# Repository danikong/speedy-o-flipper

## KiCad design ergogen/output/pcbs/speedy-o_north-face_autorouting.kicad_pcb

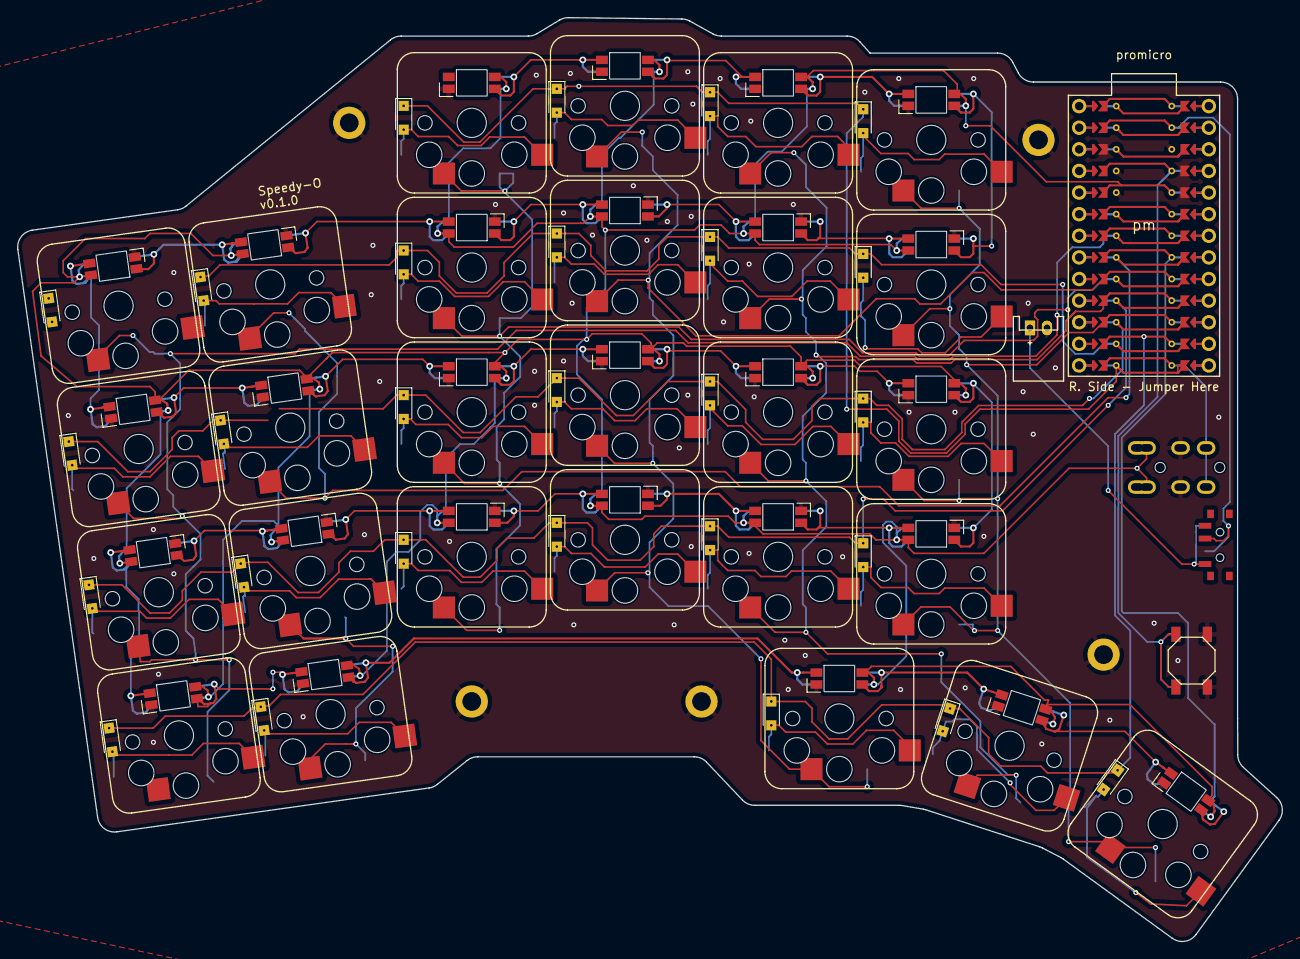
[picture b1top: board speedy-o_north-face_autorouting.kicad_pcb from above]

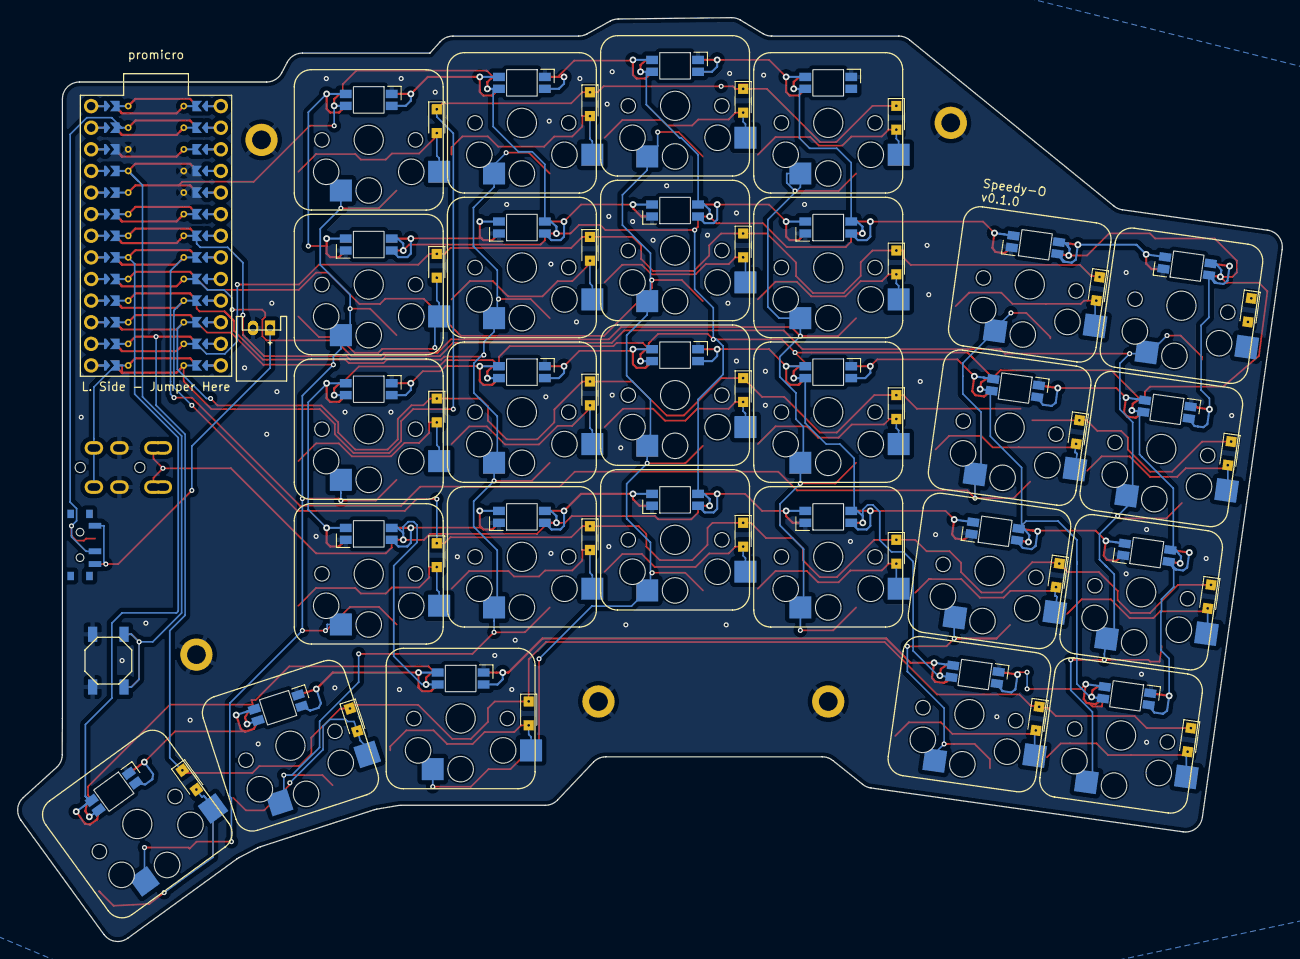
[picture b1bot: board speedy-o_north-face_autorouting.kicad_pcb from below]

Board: 2 copper layers, 148.6 x 108.6 mm, 93 parts (27 on the bottom side), 71 nets.

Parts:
B1, B2: SW_TACT_ALPS_SKQGABE010
D1, D2, D3, D4, D5, D6, D7, D8, D9, D10, D11, D12, D13, D14, D15, D16, D17, D18, D19, D20, D21, D22, D23, D24, D25, D26, D27: Nexperia_CFP3_SOD-123W
H1, H2, H3, H4, H5: mounting_hole_plated
JST1, JST2: JST_PH_S2B-PH-K_02x2.00mm_Angled
LED1, LED2, LED3, LED4, LED5, LED6, LED7, LED8, LED9, LED10, LED11, LED12, LED13, LED14, LED15, LED16, LED17, LED18, LED19, LED20, LED21, LED22, LED23, LED24, LED25, LED26, LED27: led_SK6812mini-e (per-key, reversible)
S1, S2, S3, S4, S5, S6, S7, S8, S9, S10, S11, S12, S13, S14, S15, S16, S17, S18, S19, S20, S21, S22, S23, S24, S25, S26, S27: PG1350
T1: SW_SPDT_PCM12
TRRS: TRRS-PJ-320A-dual
pm: ProMicro

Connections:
GND: B1.1, B2.1, JST1.2, JST2.2, LED1.3, LED2.3, LED3.3, LED4.3, LED5.3, LED6.3, LED7.3, LED8.3, LED9.3, LED10.3, LED11.3, LED12.3, LED13.3, LED14.3, LED15.3, LED16.3, LED17.3, LED18.3, LED19.3, LED20.3, LED21.3, LED22.3, LED23.3, LED24.3, LED25.3, LED26.3, LED27.3, TRRS.3, pm.3, pm.4, pm.23
P3: S1.1, S2.1, S3.1, S4.1, pm.6
P4: S5.1, S6.1, S7.1, S8.1, pm.7
P5: S9.1, S10.1, S11.1, S12.1, pm.8
P6: D1.1, D5.1, D10.1, D14.1, D17.1, D21.1, pm.9
P7: D2.1, D6.1, D11.1, D15.1, D18.1, D22.1, pm.10
P8: D3.1, D7.1, D12.1, D16.1, D19.1, D23.1, pm.11
P9: D4.1, D8.1, D20.1, D24.1, pm.12
P10: TRRS.4, pm.13
P14: S21.1, S22.1, S23.1, S24.1, S27.1, pm.15
P15: S17.1, S18.1, S19.1, S20.1, S26.1, pm.16
P16: D9.1, D13.1, D25.1, D26.1, D27.1, pm.14
P18: S13.1, S14.1, S15.1, S16.1, S25.1, pm.17
P19: LED27.2, pm.18
RAW: T1.2, pm.24
RST: B1.2, B2.2, pm.22
VCC: LED1.1, LED2.1, LED3.1, LED4.1, LED5.1, LED6.1, LED7.1, LED8.1, LED9.1, LED10.1, LED11.1, LED12.1, LED13.1, LED14.1, LED15.1, LED16.1, LED17.1, LED18.1, LED19.1, LED20.1, LED21.1, LED22.1, LED23.1, LED24.1, LED25.1, LED26.1, LED27.1, TRRS.2, pm.21
main_index_bottom: D1.2, S17.2
main_index_home: D2.2, S18.2
main_index_num: D4.2, S20.2
main_index_top: D3.2, S19.2
main_inner_bottom: D5.2, S21.2
main_inner_home: D6.2, S22.2
main_inner_num: D8.2, S24.2
main_inner_top: D7.2, S23.2
main_middle_bottom: D21.2, S13.2
main_middle_home: D22.2, S14.2
main_middle_num: D24.2, S16.2
main_middle_top: D23.2, S15.2
main_outer_bottom: D9.2, S1.2
main_outer_home: D10.2, S2.2
main_outer_num: D12.2, S4.2
main_outer_top: D11.2, S3.2
main_pinky_bottom: D13.2, S5.2
main_pinky_home: D14.2, S6.2
main_pinky_num: D16.2, S8.2
main_pinky_top: D15.2, S7.2
main_ring_bottom: D17.2, S9.2
main_ring_home: D18.2, S10.2
main_ring_num: D20.2, S12.2
main_ring_top: D19.2, S11.2
pos: JST1.1, JST2.1, T1.1
rgb_main_index_bottom: LED13.4, LED17.2
rgb_main_index_home: LED18.2, LED22.4
rgb_main_index_num: LED20.2, LED24.4
rgb_main_index_top: LED15.4, LED19.2
rgb_main_inner_bottom: LED17.4, LED21.2
rgb_main_inner_home: LED21.4, LED22.2
rgb_main_inner_num: LED23.4, LED24.2
rgb_main_inner_top: LED19.4, LED23.2
rgb_main_middle_bottom: LED9.4, LED13.2
rgb_main_middle_home: LED14.2, LED18.4
rgb_main_middle_num: LED16.2, LED20.4
rgb_main_middle_top: LED11.4, LED15.2
rgb_main_outer_bottom: LED1.2, LED5.4
rgb_main_outer_home: LED1.4, LED2.2
rgb_main_outer_num: LED3.4, LED4.2
rgb_main_outer_top: LED3.2, LED7.4
rgb_main_pinky_bottom: LED5.2, LED25.4
rgb_main_pinky_home: LED2.4, LED6.2
rgb_main_pinky_num: LED4.4, LED8.2
rgb_main_pinky_top: LED7.2, LED10.4
rgb_main_ring_bottom: LED6.4, LED9.2
rgb_main_ring_home: LED10.2, LED14.4
rgb_main_ring_num: LED12.2, LED16.4
rgb_main_ring_top: LED8.4, LED11.2
rgb_thumb_home_home: LED26.2, LED27.4
rgb_thumb_outer_home: LED25.2, LED26.4
thumb_home_home: D26.2, S26.2
thumb_inner_home: D27.2, S27.2
thumb_outer_home: D25.2, S25.2

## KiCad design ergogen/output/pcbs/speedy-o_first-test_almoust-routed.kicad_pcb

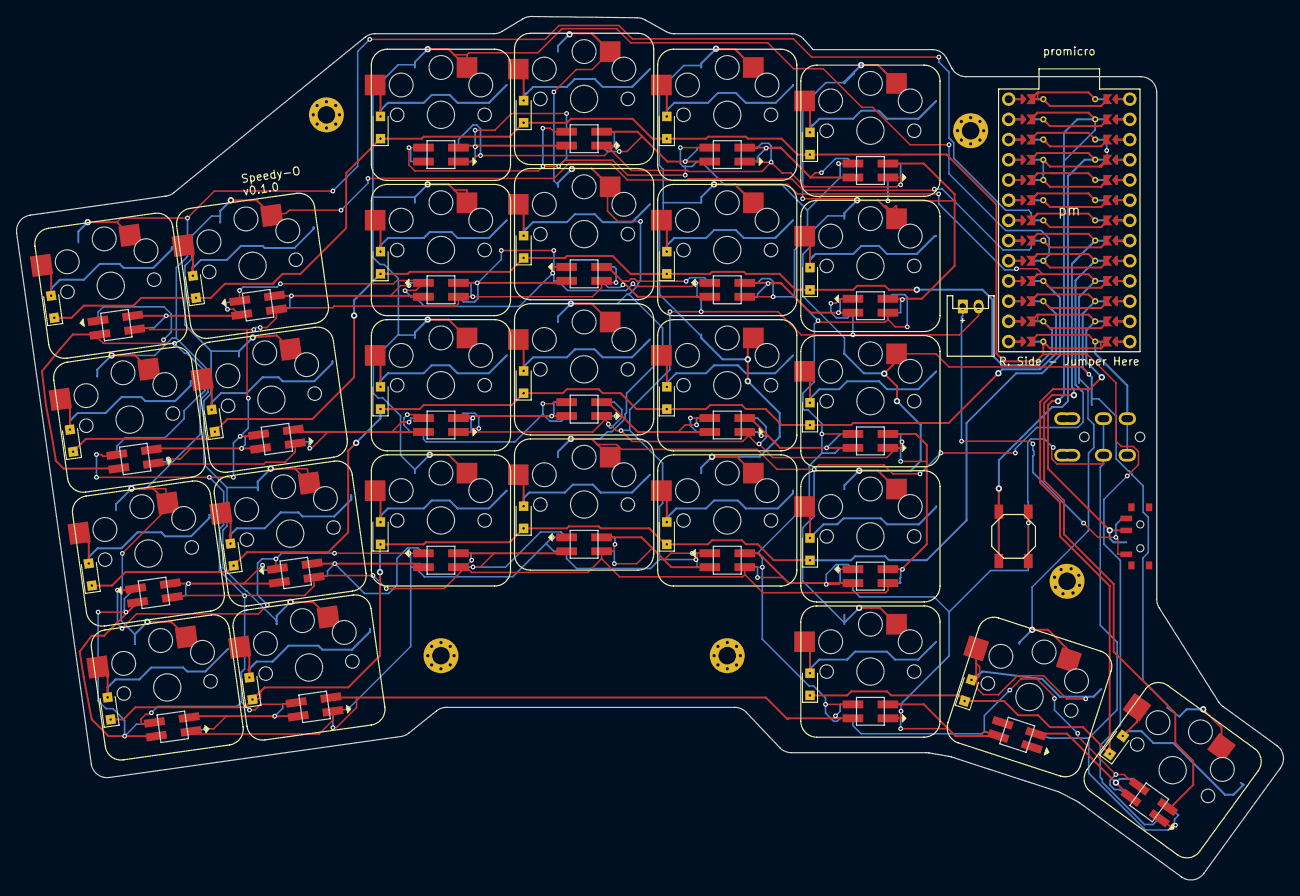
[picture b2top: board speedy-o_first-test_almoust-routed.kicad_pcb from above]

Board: 2 copper layers, 159.3 x 108.6 mm, 93 parts (0 on the bottom side), 71 nets.

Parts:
B1, B2: SW_TACT_ALPS_SKQGABE010
D1, D2, D3, D4, D5, D6, D7, D8, D9, D10, D11, D12, D13, D14, D15, D16, D17, D18, D19, D20, D21, D22, D23, D24, D25, D26, D27: Nexperia_CFP3_SOD-123W
JST1, JST2: JST_PH_S2B-PH-K_02x2.00mm_Angled
LED1, LED2, LED3, LED4, LED5, LED6, LED7, LED8, LED9, LED10, LED11, LED12, LED13, LED14, LED15, LED16, LED17, LED18, LED19, LED20, LED21, LED22, LED23, LED24, LED25, LED26, LED27: WS2812B
S1, S2, S3, S4, S5, S6, S7, S8, S9, S10, S11, S12, S13, S14, S15, S16, S17, S18, S19, S20, S21, S22, S23, S24, S25, S26, S27: PG1350
T1: SW_SPDT_PCM12
TRRS1: TRRS-PJ-320A-dual
_2, _3, _4, _5, _6: MountingHole_2.2mm_M2_Pad_Via
pm: ProMicro

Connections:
GND: B1.1, B2.1, JST1.2, JST2.2, LED1.3, LED2.3, LED3.3, LED4.3, LED5.3, LED6.3, LED7.3, LED8.3, LED9.3, LED10.3, LED11.3, LED12.3, LED13.3, LED14.3, LED15.3, LED16.3, LED17.3, LED18.3, LED19.3, LED20.3, LED21.3, LED22.3, LED23.3, LED24.3, LED25.3, LED26.3, LED27.3, TRRS1.3, pm.3, pm.4, pm.23
P3: S1.1, S2.1, S3.1, S4.1, pm.6
P4: S5.1, S6.1, S7.1, S8.1, pm.7
P5: S9.1, S10.1, S11.1, S12.1, pm.8
P6: D1.1, D5.1, D9.1, D13.1, D17.1, D21.1, pm.9
P7: D2.1, D6.1, D10.1, D14.1, D18.1, D22.1, pm.10
P8: D3.1, D7.1, D11.1, D15.1, D19.1, D23.1, pm.11
P9: D4.1, D8.1, D12.1, D16.1, D20.1, D24.1, LED27.4, pm.12
P10: TRRS1.4, pm.13
P14: S21.1, S22.1, S23.1, S24.1, S27.1, pm.15
P15: S17.1, S18.1, S19.1, S20.1, S26.1, pm.16
P16: D25.1, D26.1, D27.1, pm.14
P18: S13.1, S14.1, S15.1, S16.1, S25.1, pm.17
P19: LED27.4, pm.18
RAW: T1.2, pm.24
RST: B1.2, B2.2, pm.22
VCC: LED1.1, LED2.1, LED3.1, LED4.1, LED5.1, LED6.1, LED7.1, LED8.1, LED9.1, LED10.1, LED11.1, LED12.1, LED13.1, LED14.1, LED15.1, LED16.1, LED17.1, LED18.1, LED19.1, LED20.1, LED21.1, LED22.1, LED23.1, LED24.1, LED25.1, LED26.1, LED27.1, TRRS1.2, pm.21
main_index_bottom: D17.2, S17.2
main_index_home: D18.2, S18.2
main_index_num: D20.2, S20.2
main_index_top: D19.2, S19.2
main_inner_bottom: D21.2, S21.2
main_inner_home: D22.2, S22.2
main_inner_num: D24.2, S24.2
main_inner_top: D23.2, S23.2
main_middle_bottom: D13.2, S13.2
main_middle_home: D14.2, S14.2
main_middle_num: D16.2, S16.2
main_middle_top: D15.2, S15.2
main_outer_bottom: D1.2, S1.2
main_outer_home: D2.2, S2.2
main_outer_num: D4.2, S4.2
main_outer_top: D3.2, S3.2
main_pinky_bottom: D5.2, S5.2
main_pinky_home: D6.2, S6.2
main_pinky_num: D8.2, S8.2
main_pinky_top: D7.2, S7.2
main_ring_bottom: D9.2, S9.2
main_ring_home: D10.2, S10.2
main_ring_num: D12.2, S12.2
main_ring_top: D11.2, S11.2
pos: JST1.1, JST2.1, T1.1
rgb_main_index_bottom: LED13.2, LED17.4
rgb_main_index_home: LED18.4, LED22.2
rgb_main_index_num: LED20.4, LED24.2
rgb_main_index_top: LED15.2, LED19.4
rgb_main_inner_bottom: LED17.2, LED21.4
rgb_main_inner_home: LED21.2, LED22.4
rgb_main_inner_num: LED23.2, LED24.4
rgb_main_inner_top: LED19.2, LED23.4
rgb_main_middle_bottom: LED9.2, LED13.4
rgb_main_middle_home: LED14.4, LED18.2
rgb_main_middle_num: LED16.4, LED20.2
rgb_main_middle_top: LED11.2, LED15.4
rgb_main_outer_bottom: LED1.4, LED5.2
rgb_main_outer_home: LED1.2, LED2.4
rgb_main_outer_num: LED3.2, LED4.4
rgb_main_outer_top: LED3.4, LED7.2
rgb_main_pinky_bottom: LED5.4, LED25.2
rgb_main_pinky_home: LED2.2, LED6.4
rgb_main_pinky_num: LED4.2, LED8.4
rgb_main_pinky_top: LED7.4, LED10.2
rgb_main_ring_bottom: LED6.2, LED9.4
rgb_main_ring_home: LED10.4, LED14.2
rgb_main_ring_num: LED12.4, LED16.2
rgb_main_ring_top: LED8.2, LED11.4
rgb_thumb_home_home: LED26.4, LED27.2
rgb_thumb_outer_home: LED25.4, LED26.2
thumb_home_home: D26.2, S26.2
thumb_inner_home: D27.2, S27.2
thumb_outer_home: D25.2, S25.2

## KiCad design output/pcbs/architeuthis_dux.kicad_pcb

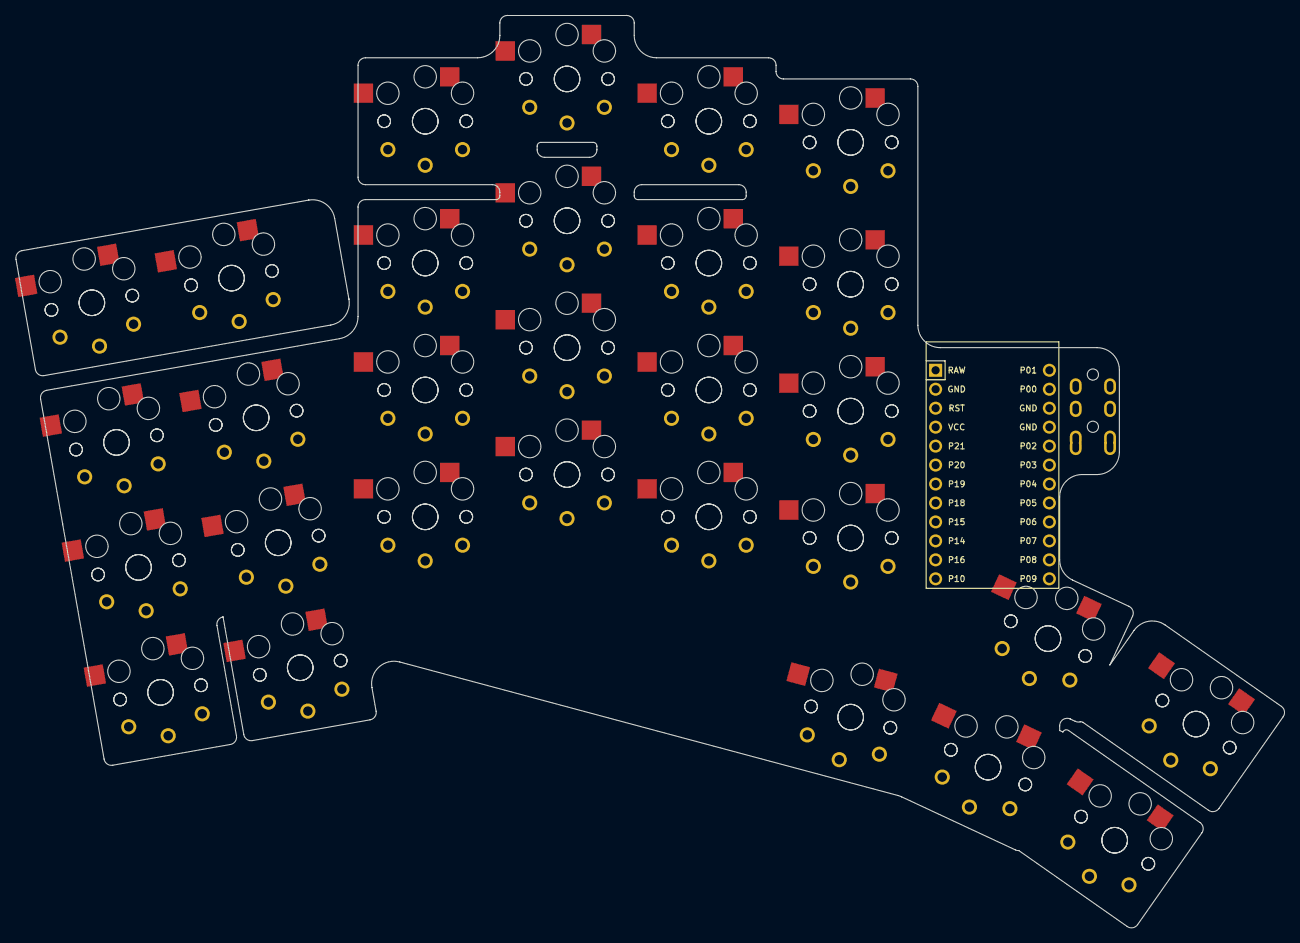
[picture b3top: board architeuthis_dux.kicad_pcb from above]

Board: 2 copper layers, 170.0 x 122.2 mm, 60 parts (0 on the bottom side), 4 nets, no tracks yet.

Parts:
MCU1: ProMicro
S1, S2, S3, S4, S5, S6, S7, S8, S9, S10, S11, S12, S13, S14, S15, S16, S17, S18, S19, S20, S21, S22, S23, S24, S25, S26, S27, S28, S29, S30, S31, S32, S33, S34, S35, S36, S37, S38, S39, S40, S41, S42, S43, S44, S45, S46, S47, S48, S49, S50, S51, S52, S53, S54, S55, S56, S57, S58: PG1350
TRRS1: TRRS-PJ-320A-dual

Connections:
=column_net: S1.1, S2.1, S3.1, S4.1, S5.1, S6.1, S7.1, S8.1, S9.1, S10.1, S11.1, S12.1, S13.1, S14.1, S15.1, S16.1, S17.1, S18.1, S19.1, S20.1, S21.1, S22.1, S23.1, S24.1, S25.1, S26.1, S27.1, S28.1, S29.1, S30.1, S31.1, S32.1, S33.1, S34.1, S35.1, S36.1, S37.1, S38.1, S39.1, S40.1, S41.1, S42.1, S43.1, S44.1, S45.1, S46.1, S47.1, S48.1, S49.1, S50.1, S51.1, S52.1, S53.1, S54.1, S55.1, S56.1, S57.1, S58.1
GND: MCU1.2, MCU1.15, MCU1.16, S1.2, S2.2, S3.2, S4.2, S5.2, S6.2, S7.2, S8.2, S9.2, S10.2, S11.2, S12.2, S13.2, S14.2, S15.2, S16.2, S17.2, S18.2, S19.2, S20.2, S21.2, S22.2, S23.2, S24.2, S25.2, S26.2, S27.2, S28.2, S29.2, S30.2, S31.2, S32.2, S33.2, S34.2, S35.2, S36.2, S37.2, S38.2, S39.2, S40.2, S41.2, S42.2, S43.2, S44.2, S45.2, S46.2, S47.2, S48.2, S49.2, S50.2, S51.2, S52.2, S53.2, S54.2, S55.2, S56.2, S57.2, S58.2, TRRS1.1, TRRS1.2
P2: MCU1.17, TRRS1.3
VCC: MCU1.4, TRRS1.4

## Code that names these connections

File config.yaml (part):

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                        home:
                            row_net: P6
                            led_in: "rgb_{{name}}"
                            led_out: rgb_main_pinky_home
                        top:
                            row_net: P7
                            led_in: "rgb_{{name}}"
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                        num:
                            row_net: P8
                            led_in: "rgb_{{name}}"
                            led_out: rgb_main_pinky_num
                pinky:
                    key:
                        col_net: P4
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                            led_out: rgb_main_middle_bottom
                        home:
                            led_in: "rgb_{{name}}"
                            led_out: rgb_main_pinky_top
                        top:
                            led_in: "rgb_{{name}}"
                            led_out: rgb_main_middle_top
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                outer.key:
                    col_net: P18
                    led_in: "rgb_{{name}}"
                    led_out: rgb_main_pinky_bottom
                    spread: cx
                home.key:
                    col_net: P15
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        front_text: &text
            what: text
            where: &textWhere
                ref: main_pinky_num
                shift: [0, 0.6cy]
            params: &textParams
                text: Speedy-O\nv0.1.0
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
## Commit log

2024-09-17 outline created
2024-09-18 changed outline
2024-09-18 add connection and switch to nice nano
2024-12-16 submit old config
2024-12-16 new config
2024-12-26 update config
2024-12-26 alternative layout
2024-12-26 update routing
2024-12-26 add reset button on the back
2024-12-26 update position of components
2024-12-27 add other footprints
2024-12-28 first satisfying layout
2025-01-13 add zmk
2025-01-13 rename zmk folder
2025-01-13 move github action files
2025-01-13 move files
